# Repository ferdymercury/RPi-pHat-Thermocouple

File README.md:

# Raspberry Pi Thermocouple pHat for genmon

## Thanks!

First and foremost, this project is a derivation of the fine work done by
[Mike Lawrence](https://github.com/mikelawrence) with his
[RPi-pHat-Thermocouple](https://github.com/mikelawrence/RPi-pHat-Thermocouple)
project.  His implementation has a different use-case, and I adapted his
great design for my own purposes.

The major changes from his design to this one are:

* Change the form-factor from a Raspberry-Pi Zero sized board to a "full size"
  version intended for a Raspberry Pi 2 or Raspberry 3.
* Add an isolated RS-232 to TTL interface.
* Drop the on-board regulator to 5V, and associated bridge rectifier and "ideal
  diode".
* Drop the SPI EEPROM for automated "Hat" configuration.
* Drop the alarm buzzer.
* Add screw terminal connections for power, thermocouple, off-board 1-wire bus
  peripherals and RS-232 connections.
* Add pin headers for driving LED annunciators.
* Add pin headers (with configurable pull-ups) for end-user supplied I2C
  peripherals.
* Add a fuse to protect connections to off-board peripherals.

**IMPORTANT**

Please note that all of the work described here is on the `genmon` branch 
of the git repository.  Make sure that you `git checkout genmon` if you
clone the repository to get this modified version.

I'd like to extend my thanks to [Mike](https://github.com/mikelawrence) for
sharing his work with the community under an [MIT license](LICENSE).  This
derivitive project is likewise available under the same license.  

# What it is

This is a Raspberry Pi PCB that supports:

* Three MAX31850 1-Wire Thermocouple Converters for remote temperature sensing
* DS18S20 1-Wire Thermometer for local Hat temperature
* Electrically isolated RS-232 interface to the Raspberry Pi's serial port UART.

The goal of this board is to piggyback on a Raspberry Pi running the
[genmon](https://github.com/jgyates/genmon) package.  That software expects to
communicate with the 9600 bps RS-232 serial MODBUS connection on a Generac
generator controller.

Additionally, there are 3 type K thermocouple interfaces which can be used to
monitor critical temperatures in the generator, such as the oil cooler
temperature, exhaust air temperature, body temperatore of the generator, etc.

# Why it is

I have a 22kW generator manufactured by Generac, propane fueled.  The addition
of the wonderful [genmon](https://github.com/jgyates/genmon) has really added
significant value, and allowed me to integrate the generator with my [Home
Assistant](https://home-assistant.io) home automation platform.

On one occasion, I was experiencing an extended power outage, and of course, the
generator automatically started and switch the home loads to it.  About 6 hours
into this power outage, I was wondering how it was working.  The
[genmon](https://github.com/jgyates/genmon) software provides a bunch of data on
the current operation, indicating no alarms or faults.  However, after an
extended run time, I was wondering if the generator was overheating or otherwise
being stressed?

Measuring some of the relevant components had to be done with, *e.g.,*
thermocouples since the usual Dallas Semiconductor/Maxim 1-wire bus temperature
sensors wouldn't work in a high temperature environment. It was at that time
that I stumbled upon Mike Lawarence's work and decided to adapt it.

The first thing that caused me to want to layout a new board was that my use
case was different.  I had no need for a buzzer since my Raspberry Pi was buried
inside the generator enclosure and wouldn't ever be heard.  Further, I *really*
wanted to have screw terminals for the thermocouple wires since the metal alloys
used in the thermocouple wires don't take solder easily.  Due to the vibration
inherit to the environment, I wanted to have a really robust mechanical solution
for those connections.

Finally, The Raspberry Pi running [genmon](https://github.com/jgyates/genmon)
requires a conneciton to the RS-232 signals on the generator controller's MODBUS
interface.  At present, I was using an external TTL/RS-232 level convertor for
this purpose.  However in connecting this up, I create a ground loop -- there's
a ground path from the generator controller through the RS-232 level converter,
though the Raspberry Pi, through the 12V to 5V USB power support, to the
negative battery terminal, and finally through the cable from the battery to the
generator starter and control electronics.  I shudder to think how this all
behaves when the starter kicks in during a generator start-up sequence.

So this led to an isolated RS-232 to TTL level converter.  There is a separate
power support for this part of the circuit, intended to be supplied by power
available on the generator controller's MODBUS accessory connector.  There is an
high-speed isolation device (apparently transformer coupled?) rated at
approximately 20MBit/s, substantially higher bandwidth than most common
optoisolators.  This isolation device has separate power/ground connections for
each side, and in excess of 1kV of isolation.

# Status

A schematic for this circuit is available in [PDF format](RPi-pHat-Thermocouple.pdf)
so you don't need to use KiCAD to casually examine what's going on.

## Genmon variation

* Rev 3.1 of the PCB fixes pin assignment problems on the Maxim MAX3221
  RS-232/TTL level converter device.
  * You can order parts from Mouser using this [shared
    BOM](https://www.mouser.com/ProjectManager/ProjectDetail.aspx?AccessID=b36514df12)
    link. 
* Rev 3.0 PCB was the first version of the whole redesign, manufactured by
  JCLPCB.

Please note that all of the work described here is on the `genmon` branch 
of the git repository.  Make sure that you `git checkout genmon` if you
clone the repository to get this modified version.

## Original version
Older versions described below are Mike Lawrence's original design in the smaller Raspberry Pi Zero sized
form factor.

* Rev 2.0 PCB has been ordered from OSH Park and has been fully tested.
  * Removed one of the four MAX31850K's.
  * Increased thermocouple input filtering buy adding ferrite beads and a larger capacitor.
  * Added more filtering to thermocouple side of MAX31850K's.
  * Added DC Power connector and switching power supply that powers both the Raspberry Pi and the Hat.
  * The noisy reading the MAX31850K's occasionaly get are reduced in this version but not gone.
  * You can order parts from Mouser using this [shared BOM](https://www.mouser.com/ProjectManager/ProjectDetail.aspx?AccessID=bd69c35967).
  * You can order the PCB from OSH Park using this [link](https://oshpark.com/shared_projects/meYar6Ji).
* Rev 1.2 PCB has been ordered from OSH Park and tested.
  * Discovered the MAX31850K's get a noisy reading about 0.1% of the time. This noise is typically within 5 C but sometimes is greater than 30 C. Adding capacitors did little to help the Rev 1.1 design so most of the 3.3V power was switched to a 3.3V LDO regulator in an attempt to reduce the noise on the 3.3V power seen by the MAX31850K's.
  * You can order parts from Mouser using this [shared BOM](http://www.mouser.com/ProjectManager/ProjectDetail.aspx?AccessID=7612d46eeb).
  * You can order the PCB from OSH Park using this [link](https://oshpark.com/shared_projects/S5a4ZDvw).
* Rev 1.1 PCB was never built.
  * Added a pulldown on the alert signal to prevent the Alert buzzer from sounding on power on.
  * Added an on board DS18S20.
* Rev 1.0 PCB has been ordered from OSH Park and tested.
  * Discovered the linux kernel doesn't seem to support MAX31850K devices without a DS18S20 present. The kernel detects the MAX31850K devices but does not create a w1_slave file to read the temperature. This is most likely a bug in the Linux W1 driver.

# Kicad Notes

* This PCB design uses some libraries available here [Mike's KiCad Libraries](https://github.com/mikelawrence/KiCad-Libraries).
* This PCB was designed with [KiCad 5.1.5](http://kicad.org).
* The MAX31850K parts have an exposed pad on the bottom which requires either a
  reflow oven or hot air to solder properly.  Be careful to not apply too much
  solder paste to this pad.

# Design

## Input Power

This board has screw terminals to which you can connect a **regulated 5VDC**
power supply.  This is is connected **directlly** to the +5V power pins on the
Raspberry Pi GPIO connector.

**You should _never_ connect 5V DC power to the screw terminals if the Raspberry
Pi is being powered via it's USB connector!**

If the Raspberry Pi is powered in the usual way via its micro USB connector,
then the Raspberry Pi will supply power to this PCB and power the components on
the board.  Alternatively, if it is more convienient to provide regulated +5V DC
power from another source, then the screw terminals are available for that
purpose.

The components on the board draw well under 100mA of power at 5V, so there ought
to be no concern when powering from the Raspberry Pi that the PCB is plugged
into.

## Isolated RS-232 interface

Separately, there is a 4 pin screw terminal connection for RS-232 transmit and
receive as well as generator controller ground and generator controller 5VDC.
The ground and power on this 4 position screw terminal is isolated and distinct
from the Raspberry Pi power and the rest of the PCB.  You should not tie the
ground on the RS-232 screw termainal block to any other ground connection on the
genmon PCB.

## MAX31850K Thermocouple-to-Digital Converter

Although the MAX38150K datasheet typical application circuit doesn't show the
use of ferrite beads many designs seems to include them. That in combination
with the larger than normal capacitor across the input will hopefully improve
sampling errors even further.

# Raspberry Pi Setup

This setup makes several assumptions. First you are using Raspbian Buster. This
software and instructions most likely work on other versions of Raspbian but
they have not been tested. Second Python3 is the target programming environment.
It is also assumed that you are using the standard `pi` user. Otherwise you will
have to edit the commands by replacing `/home/pi` with your user's home
directory. Install everything needed by executing the following commands.

```text
sudo apt update
sudo apt -y install git python3-rpi.gpio python3-w1thermsensor python3-paho-mqtt
```

## Get the repository from Github

Clone this repository from Github with the following commands.

```text
cd /home/pi
git clone https://github.com/lmamakos/RPi-pHat-Thermocouple
git checkout genmon
```

## Setup Interfaces

For this Hat you will need to enable the 1-Wire interface. From the command line type
`sudo raspi-config` and follow the prompts to install  support in the kernel.

It's time to reboot your Raspberry Pi with `sudo reboot`.

## Test the 1-Wire Temperature Sensors

[Python3-w1thermsensor](https://github.com/timofurrer/w1thermsensor) is a nice 1-Wire python library that also supports command line reading of temperatures from 1-Wire devices. You should have already installed this package in the [Raspberry Pi Setup](#Raspberry-Pi-Setup) section.

Test the single on-board DS18B20 temperature sensor using `w1thermsensor all --type DS18S20`.

```text
pi@studio-fridge:~ $ w1thermsensor all --type DS18S20
Got temperatures of 1 sensors:
  Sensor 1 (00080372f2c4) measured temperature: 28.06 celsius
```

Now test the three MAX38150Ks temperature sensor by using `w1thermsensor all --type MAX31850K`.

```text
pi@studio-fridge:~ $ w1thermsensor all --type MAX31850K
Got temperatures of 3 sensors:
  Sensor 1 (000000181928) measured temperature: 23.75 celsius
  Sensor 2 (00000018192b) measured temperature: 24.0 celsius
  Sensor 3 (000000181d59) measured temperature: 2047.81 celsius
```

The 2047.81 celsius reading is what you get when there is no thermocouple connected to the MAX31850K.

# Integration with other software packages and systems

## Integration with [genmon](https://github.com/jgyates/genmon)

The primary motivation for this board's design is to support the use of
[genmon](https://github.com/jgyates/genmon) running on a Raspberry Pi 2 Model B,
Raspberry Pi 3 Model B, or a Raspberry Pi Zero.  It includes two major
functional elements:

1. Three (3) connections for Type-K thermocouples, using a Maxim 1-wire bus
   attached controller.
2. A TTL to RS-232 level converted to connect the Raspberry Pi serial port to
   the MODBUS connection on the generator controller.

### Thermocouples

These are intended to enable monitoring of high-temperature points within the
Generac generator, such as the temperature of the engine oil cooler, engine
block, generator temperature or perhaps exhaust temperature.

The use of Type-K thermocouples permits the measurement of very high
temperatures, as high as 700 °C.  As a practical matter, the maximum temperature
is limited by the insulation and jacket on the cabling connecting to the
thermocouple junction.  Typically, thermocouple products with cables rated to
400 °C are easily available and inexpensive.

**VERY IMPORTANT** - the MAX 31855K thermocouple interface devices does not
support *grounded thermocouples* - where the junction of the thermocouple is
electrically connected to the power supply ground.  In particular, the sensor
device does a diagnostic test checking for an "open" connection at the
thermocouple terminals, as well as a short to ground or the *V<sub>dd</sub>*
power supply on the board.

It's common to see either exposed junction thermocouples, or where the actual
thermocouple junction is within a metal tube or other mechanical arrangement.
The junction is deliberately tied to the case (which presumably is in contact
with the thing you're trying to measure) for better thermoconducivity, making it
more responsive to temperature changes.  Additionally some thermocouple probe
arrangements have a woven metalic armor shield on the cable, which is also
electrically tied to the thermocouple junction. If these armored cables come in
contact with each other, this will also cause a fault.

It is recommended that you choose a Type-K thermocouple with a high (enough)
temperature rated cable, and either have the thermocouple junction be in free
space, or insulated from the chassis of the generator.

One possibility if you use the inexpensive generic thermocouple probes is to
form a small bead of high temperature expoxy around the junction, or affix the
the junction with non-conductive expoxy to the surface you're trying to perform
temperature measurements on.

### DS18B20 or DS18S20 1-wire bus sensors

Why not the usual Maxim DS18B20 one-wire bus temperature sensors?  These
semiconductor devices are packaged in plastic material for their packages, and
not rated for these high temperatures present in some parts of the generator.
However, there are other temperatures that might usefully be monitored, such as
the outside air temperature and these DS18B20 devices are entirely suitable for
that purpose.  One of these devices is present on the printed circuit board to
monitor the temperature nearby the Raspberry Pi.

### Isolated RS-232C to TTL serial converter

This board features a level converter to connect the RS-232C serial signals on
the generator's MODBUS accessory connector to the 3.3V TTL signal levels needed
by the Raspberry Pi's serial interfaces.

Most significantly, this serial interface is electrically isolated from the
Raspberry Pi and its power supply.  The RS-232 "side" is powered by the +5V /
Ground connections avialable on the MODBUS connector.  This power supply is used
to run the RS-232 level converter, and half of an isolation device which couples
the transmit and receive signals to the "other" side of the board which shares a
power supply (and ground) with the Raspberry Pi.  This isolation means that you
no longer need to worry about ground loops or powering the Raspberry Pi from
some other power source not electrically tied to the generator's power supply
and ground.

## Integration with [Home Assistant](https://home-assistant.io)

(Future) software will sample the thermocouples and 1-wire temperature sensors
and publish the values to MQTT for Home Assistant or other applications to
access.

A deliberate choice is that there is no in-built policy for over-temperature or
under-temperature warnings or actions.  The goal is to  publish these values to
be acted upon or displayed by other applications.

# Installation of the board

The board is intended to plug into the 40 pin GPIO connection available on all
the recent models of Raspberry Pi computers.   (The notable exception is the
original Raspberry Pi Model A which has a 26 pin GPIO connector.)  While it may
be possible to install a 26 pin connector on this board for that device, this
has not been tested.

Reference this rendering of the board:

### J2 - GPIO Connector

The connector mounted in this position plugs into the 40 pin GPIO expansion
connector on the Raspberry Pi.  When mounted correctly, this board sits directly
over the Raspberry Pi.

If you intend to build this board, remember that the GPIO connector is mounted
on the *back* of the board.  In fact, this is the _only_ component on the back
side of the board.

### J1 - Raspberry Pi Power

This connector supplies power to the Raspberry Pi via pins on the GPIO
connector. It should be used **only** if the Raspberry Pi doesn't have a power
supply connected to the Micro USB connector on the Raspberry Pi.  

If used, you must supply regulated +5V DC power to the connector.  Note ***there
is no reverse polarity protection*** for power fed on these screw terminals.

Power for the board can also be supplied via the Raspberry Pi's expansion connector
via the +5V DC signal on pin 2 when the Raspberry Pi is powered via it's Micro USB 
connector.

When the the PCB is powered, the green `PWR` LED D5 should be illuminated.  This
LED is conneted to the locally regulated 3.3V DC power supply for the devices on
the board (excluding the RS-232 interface; see below.)

### J3, J4, J5 - Thermocouple connections

These screw terminals are labeled **TC1**, **TC2** and **TC3**, and are
polarized.  The Type-K thermocouples connected to each of these terminals are
polarized and the positive and negative signals are labeled on the board.

The wires on the thermocouple care are usually marked or color-coded to indicate
the positive and negative termainals.  Connecting the thermocouple with reverse
polarity will not damage the board or thermocouple, but will yield incorrect
measurements.

### J7 - Generator Controller Serial Connection

Signals from the Generac generator's controller are connected to J7.  This includes the RS-232 data connections and power-supply for the isolated RS-232 interface.

An important aspect of this port, and this part of the circuit, is the electrial
isolation of the generator connection from the Raspberry Pi and the rest of the
circuit.  This interface consists of a RS-232 level converter (+/- 5V) to TTL (0
to 3.3 volts), and an isolation device that literally bridges a gap on the PCB.
The power and ground connections of this serial interface are isolated from the
power and ground connections of the Raspberry Pi and rest of the circuit.

* **RX in** this terminal is for receiving the data transmitted *from* the generator
*to* genmon.   This should be connected to pin 8 of the controller's molex connector.
* **RX out** this terminal is the *output* data transmitted *to* the generator from genmon.  This should be connected to pin 7 of the controller's molex connector.

* The **Ground** terminal should be connected to pin 2 of the controller's molex connector.
* The **5V** terminal should be connected to pin 1 of the controller's molex
  connector, which is a power source intended to power accessories.  This
  circuit requires approximately 50mA (or less) from the power input.  While a
  nominal +5V DC source is expected, there is an internal low-dropout (LDO)
  regulator on the board that should function with a 4V - 16V DC power input.
  Do not exceed 16VDC input.  This power supply connection includes a
  reverse-polarity protection diode.

When power is correctly connected, a green LED `Gen PWR` D20 should illuminate.

### J6 - External 1-wire bus connector

External 1-wire bus temperature sensors can be connected to J6.  There is
regulated +3.3V power on this connector, supplied through a 100mA resettable
thermal fuse.  This power source is intended to supply only low-power sensor
devices.

Note that the usual Maxim DS18B20 sensors are measuring temperatures between
-55C to +125C.

### J8 - LED connector

This connector is intended to drive up to 6 LEDs to be used to indicate generator status.  A selection of the Raspberry Pi CPU's GPIO signals are present: 23, 24,25, 8, 9, 7 as marked on the PCB above the connector location.  The corresponding pins below are all connected to ground.

Each active (non-ground) pin on the connector is driven through a 330 ohm current limiting resistor.  This is to try to avoid over-current situations which could damage the drivers on the CPU chip.

A 1.8V voltage drop LED should be suitable for use (which may exclude any blue
LEDs).  Typical current through the LED will be 4.5mA; while not terribly bright, this may be useful as a local status indication.

Of course, these signals could also be used to drive, e.g., a MOSFET device, to drive a higher-current load.

One possibility for using this connector to drive one or more LEDs is the
gengpio.py program, suitably configured.  
(See https://github.com/jgyates/genmon/wiki/1----Software-Overview#gengpiopy-optional )

Note that when using these signals, they can be identified by either the GPIO signal number or the pin number on the Raspberry Pi's expansion connector.  This document
only references the CPU GPIO number.

### J9 I2C expansion connector

This connector exposes an I2C interface on the Raspberry Pi's CPU for some 
future unspecified use.  By default, there are pull-up resistors on the **SDA** and 
**SCL** signals on the connector, as well as (fused) +3.3V DC and Ground.

* SDA signal is connected directly to GPIO2 (pin 3 on the Raspberry Pi connector)
* SCL signal is connected directly to GPIO3 (pin 5 on the Raspberry Pi connector)

If pull-ups on the SCL and SDA signals are not desired, then jumper traces s on
*the back* of the PCB can be cut to disconnect the pull-up resistors.

# NO WARRANTY

This project was created for my personal use, but it is available under a
permissive [license](LICENSE) to anyone interested.

This software, hardware designs and other information are provided for
educational and informational purposes only. Connecting any device to a Raspberry
Pi or generator carryies risk, and you should understand those risks before
undertaking that action.  Interconnection of this design to any other devices
provided by any manufacturer may void any warrantee offered by a manufacturer,
or cause damage if performed.  You are solely responsible for exercising due
care and caution when choosing to use these designs and other information
provided here.

**THIS HARDWARE DESIGN, SOFTWARE AND OTHER MATERIAL IS PROVIDED BY THE COPYRIGHT
HOLDERS AND CONTRIBUTORS “AS IS” AND ANY EXPRESS OR IMPLIED WARRANTIES,
INCLUDING, BUT NOT LIMITED TO, THE IMPLIED WARRANTIES OF MERCHANTABILITY AND
FITNESS FOR A PARTICULAR PURPOSE AND NONINFRINGEMENT ARE DISCLAIMED. IN NO EVENT
SHALL THE COPYRIGHT OWNER OR CONTRIBUTORS BE LIABLE FOR ANY DIRECT, INDIRECT,
INCIDENTAL, SPECIAL, EXEMPLARY, OR CONSEQUENTIAL DAMAGES (INCLUDING, BUT NOT
LIMITED TO, PROCUREMENT OF SUBSTITUTE GOODS OR SERVICES; LOSS OF USE, DATA, OR
PROFITS; OR BUSINESS INTERRUPTION) HOWEVER CAUSED AND ON ANY THEORY OF
LIABILITY, WHETHER IN CONTRACT, STRICT LIABILITY, OR TORT (INCLUDING NEGLIGENCE
OR OTHERWISE) ARISING IN ANY WAY OUT OF THE USE OF THIS SOFTWARE OR HARDWARE
DESIGNS OR OTHER MATERIALS, EVEN IF ADVISED OF THE POSSIBILITY OF SUCH DAMAGE.**

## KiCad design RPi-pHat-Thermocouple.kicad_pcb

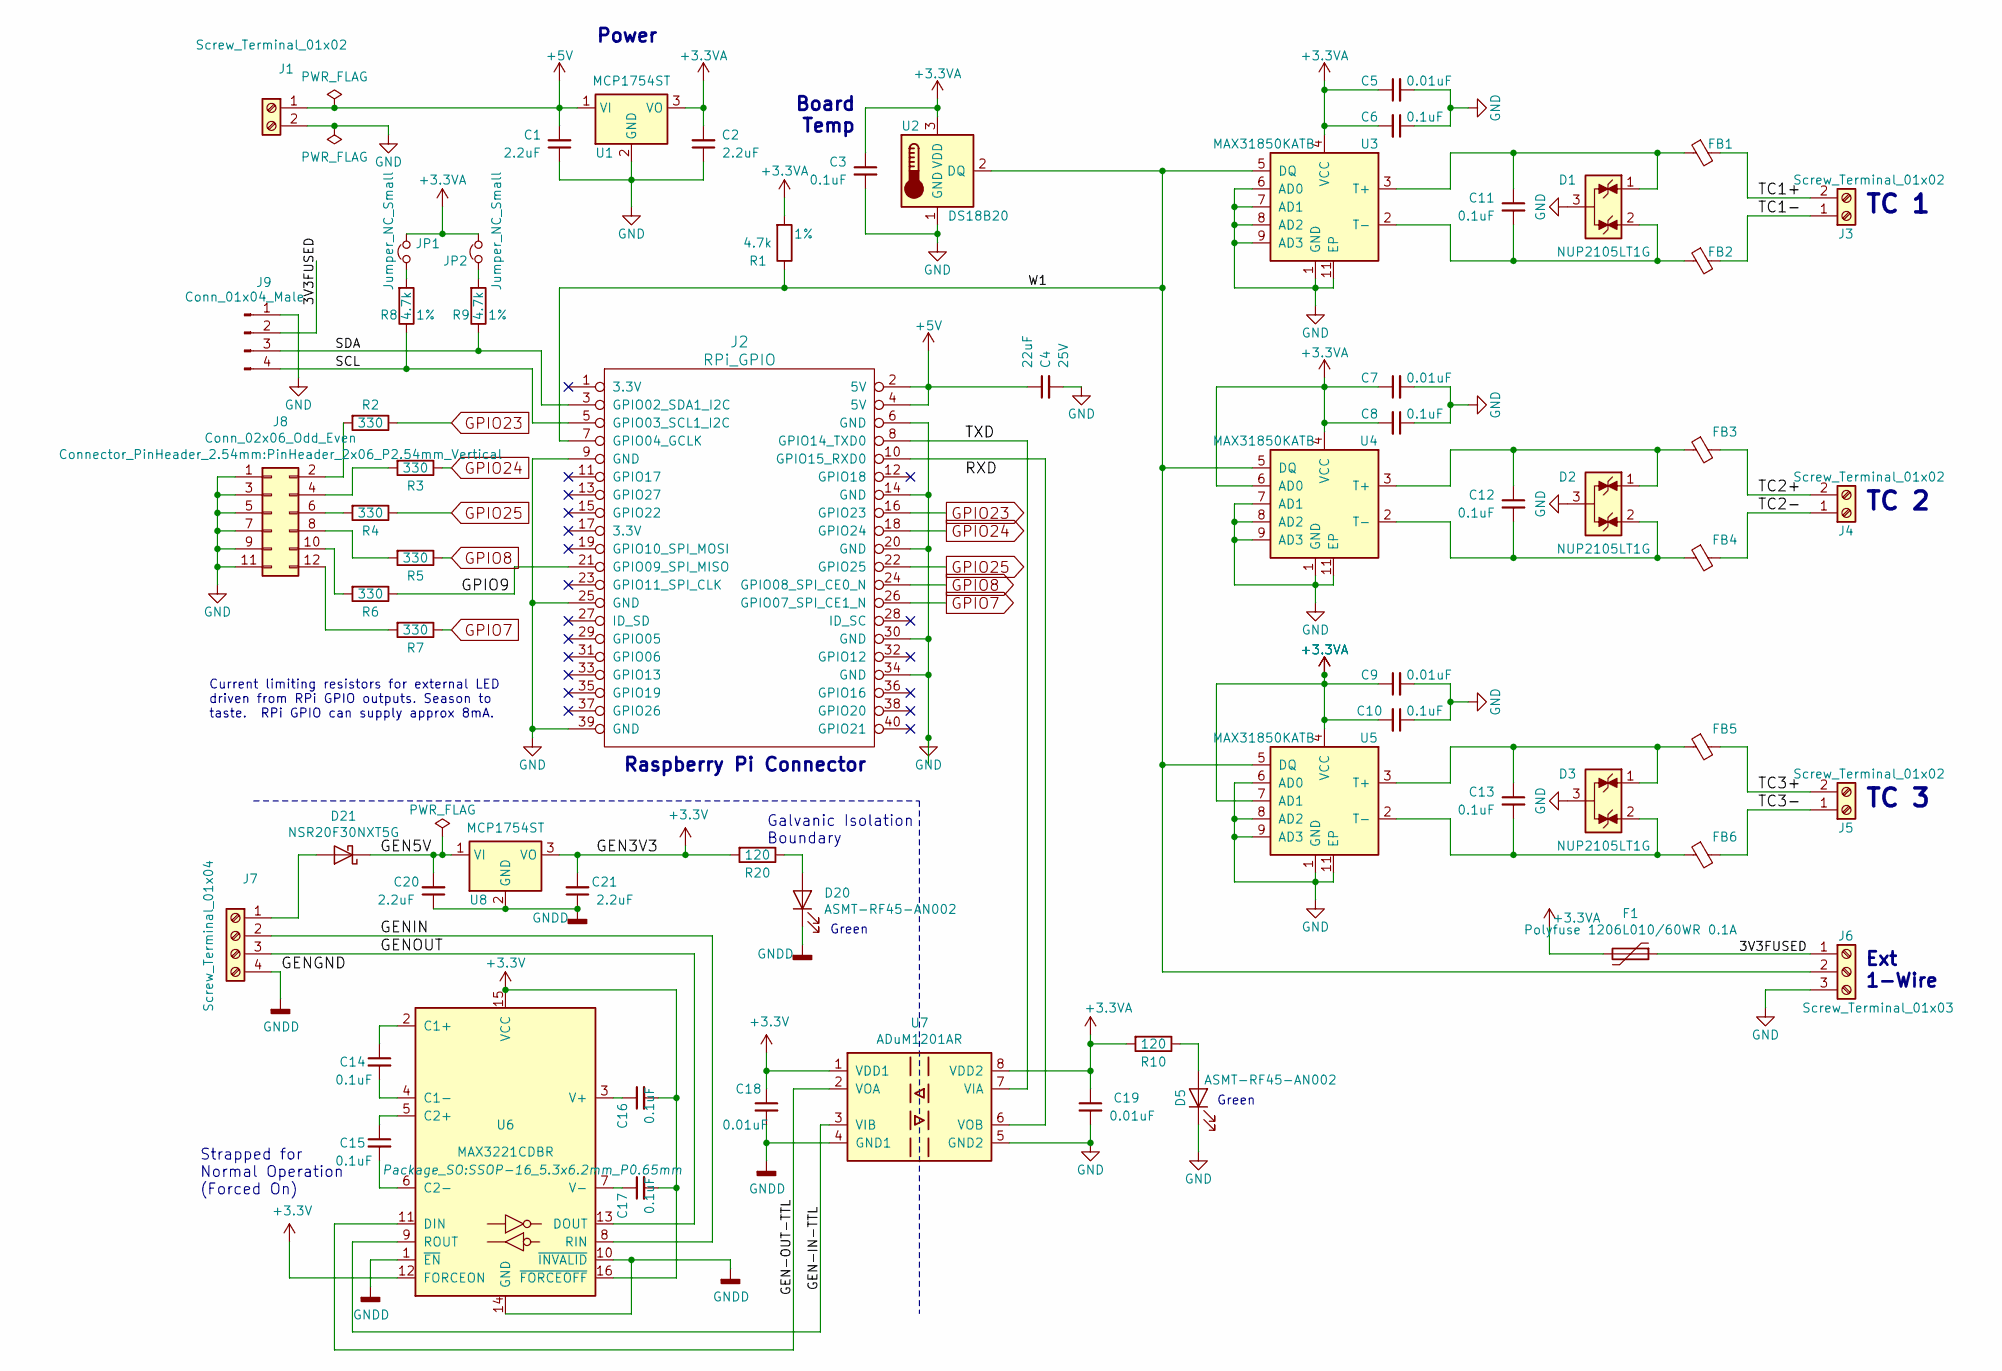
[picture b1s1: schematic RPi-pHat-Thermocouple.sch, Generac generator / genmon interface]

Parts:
C1, C2, C20, C21: 2.2uF; C_0805_2012Metric; Part Number CC0805KKX7R7BB225
C3, C6, C8, C10, C11, C12, C13, C14, C15, C16, C17: 0.1uF; C_0603_1608Metric; Part Number CC0603KRX7R9BB104
C4: 22uF; C_0805_2012Metric; Voltage 25V; Tolerance 20%; Part Number TMK212BBJ226MG-TT
C5, C7, C9, C18, C19: 0.01uF; C_0603_1608Metric; Part Number CC0603KRX7R9BB103
D1, D2, D3: NUP2105LT1G; SOT-23; Part Number NUP2105LT1G
D5, D20: ASMT-RF45-AN002; LED_0603_1608Metric; Part Number ASMT-RF45-AN002
D21: NSR20F30NXT5G; D_0603_1608Metric; Part Number NSR20F30NXT5G
F1: Polyfuse 1206L010/60WR 0.1A; Fuse_1206_3216Metric_Pad1.42x1.75mm_HandSolder; Part Number 1206L010/60WR; Mouser 576-1206L010/60WR
FB1, FB2, FB3, FB4, FB5, FB6: 1k; L_0603_1608Metric; Part Number MMZ1608B102CTD25
J1, J3, J4, J5: Screw_Terminal_01x02; TerminalBlock_Phoenix_PT-1,5-2-3.5-H_1x02_P3.50mm_Horizontal; Part Number 1984617
J2: RPi_GPIO; PinSocket_2x20_P2.54mm_Vertical; Part Number 2222
J6: Screw_Terminal_01x03; TerminalBlock_Phoenix_PT-1,5-3-3.5-H_1x03_P3.50mm_Horizontal; Part Number 1984620
J7: Screw_Terminal_01x04; TerminalBlock_Phoenix_PT-1,5-4-3.5-H_1x04_P3.50mm_Horizontal; Part Number 1984633
J8: Conn_02x06_Odd_Even; PinHeader_2x06_P2.54mm_Vertical; Part Number M20-9760642
J9: Conn_01x04_Male; PinHeader_1x04_P2.54mm_Vertical; Part Number M20-9990445
JP1, JP2: Jumper_NC_Small; SolderJumper-2_P1.3mm_Bridged_RoundedPad1.0x1.5mm
R1, R8, R9: 4.7k; R_0603_1608Metric; Tolerance 1%; Part Number AC0603FR-074K7L
R2, R3, R4, R5, R6, R7: 330; R_0603_1608Metric; Tolerance 1%; Part Number RC0603FR-07330RL
R10, R20: 120; R_0603_1608Metric; Tolerance 1%; Part Number RC0603FR-07120RL
U1, U8: MCP1754ST; SOT-89-3; Part Number MCP1754ST-3302E/MB
U2: DS18B20; TO-92; Part Number DS18B20+
U3, U4, U5: MAX31850KATB; TDFN-10-1EP_3x4mm_Pitch0.5mm; Part Number MAX31850KATB+
U6: MAX3221CDBR; SSOP-16_5.3x6.2mm_P0.65mm; Part Number MAX3221CDBR
U7: ADuM1201AR; SOIC-8_3.9x4.9mm_P1.27mm; Part Number ADUM1201AR

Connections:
+3.3VA: C2.2, C3.1, C5.1, C6.2, C7.1, C8.2, C9.1, C10.2, C19.1, F1.2, JP1.2, JP2.2, R1.2, R10.2, U1.3 (VO), U2.3 (VDD), U3.4 (VCC), U4.4 (VCC), U4.6 (AD0), U5.4 (VCC), U5.7 (AD1), U7.8 (VDD2)
+3V3: C16.2, C17.2, C18.1, C21.2, R20.2, U6.12 (FORCEON), U6.15 (VCC), U6.16 (~FORCEOFF), U7.1 (VDD1), U8.3 (VO)
+5V: C1.2, C4.1, J1.1, J2.2 (5V), J2.4 (5V), U1.1 (VI)
/3V3FUSED: F1.1, J6.1, J9.2
/GEN5V: C20.2, D21.1 (K), U8.1 (VI)
/GEN-IN-TTL: U6.9 (ROUT), U7.3 (VIB)
/GEN-OUT-TTL: U6.11 (DIN), U7.2 (VOA)
/GENIN: J7.2, U6.8 (RIN)
/GENOUT: J7.3, U6.13 (DOUT)
/GPIO9: J2.21 (GPIO09_SPI_MISO), R6.1
/SCL: J2.5 (GPIO03_SCL1_I2C), J9.4, R8.1
/SDA: J2.3 (GPIO02_SDA1_I2C), J9.3, R9.1
/TC1+: FB1.2, J3.2
/TC1-: FB2.2, J3.1
/TC2+: FB3.2, J4.2
/TC2-: FB4.2, J4.1
/TC3+: FB5.2, J5.2
/TC3-: FB6.2, J5.1
/TXD: J2.8 (GPIO14_TXD0), U7.7 (VIA)
/W1: J2.7 (GPIO04_GCLK), J6.2, R1.1, U2.2 (DQ), U3.5 (DQ), U4.5 (DQ), U5.5 (DQ)
GND: C1.1, C2.1, C3.2, C4.2, C5.2, C6.1, C7.2, C8.1, C9.2, C10.1, C19.2, D1.3 (A), D2.3 (A), D3.3 (A), D5.1 (K), J1.2, J2.6 (GND), J2.9 (GND), J2.14 (GND), J2.20 (GND), J2.25 (GND), J2.30 (GND), J2.34 (GND), J2.39 (GND), J6.3, J8.1, J8.3, J8.5, J8.7, J8.9, J8.11, J9.1, U1.2 (GND), U2.1 (GND), U3.1 (GND), U3.6 (AD0), U3.7 (AD1), U3.8 (AD2), U3.9 (AD3), U3.11 (EP), U4.1 (GND), U4.7 (AD1), U4.8 (AD2), U4.9 (AD3), U4.11 (EP), U5.1 (GND), U5.6 (AD0), U5.8 (AD2), U5.9 (AD3), U5.11 (EP), U7.5 (GND2)
GNDD: C18.2, C20.1, C21.1, D20.1 (K), J7.4, U6.1 (~EN), U6.10 (~INVALID), U6.14 (GND), U7.4 (GND1), U8.2 (GND)
GPIO7: J2.26 (GPIO07_SPI_CE1_N), R7.1
GPIO8: J2.24 (GPIO08_SPI_CE0_N), R5.1
GPIO23: J2.16 (GPIO23), R2.1
GPIO24: J2.18 (GPIO24), R3.1
GPIO25: J2.22 (GPIO25), R4.1
unnamed: C11.1, D1.1 (K), FB1.1, U3.3 (T+)
unnamed: C11.2, D1.2 (K), FB2.1, U3.2 (T-)
unnamed: C12.1, D2.1 (K), FB3.1, U4.3 (T+)
unnamed: C12.2, D2.2 (K), FB4.1, U4.2 (T-)
unnamed: C13.1, D3.1 (K), FB5.1, U5.3 (T+)
unnamed: C13.2, D3.2 (K), FB6.1, U5.2 (T-)
unnamed: C14.1, U6.2 (C1+)
unnamed: C14.2, U6.4 (C1-)
unnamed: C15.1, U6.5 (C2+)
unnamed: C15.2, U6.6 (C2-)
unnamed: C16.1, U6.3 (V+)
unnamed: C17.1, U6.7 (V-)
unnamed: D5.2 (A), R10.1
unnamed: D20.2 (A), R20.1
unnamed: D21.2 (A), J7.1
unnamed: J2.10 (GPIO15_RXD0), U7.6 (VOB)
unnamed: J8.2, R2.2
unnamed: J8.4, R3.2
unnamed: J8.6, R4.2
unnamed: J8.8, R5.2
unnamed: J8.10, R6.2
unnamed: J8.12, R7.2
unnamed: JP1.1, R8.2
unnamed: JP2.1, R9.2

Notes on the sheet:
TC 1
TC 2
TC 3
Power
Board Temp
Ext 1-Wire
Strapped for Normal Operation (Forced On)
Galvanic Isolation Boundary
Raspberry Pi Connector
Current limiting resistors for external LED driven from RPi GPIO outputs. Season to taste. RPi GPIO can supply approx 8mA.
Green

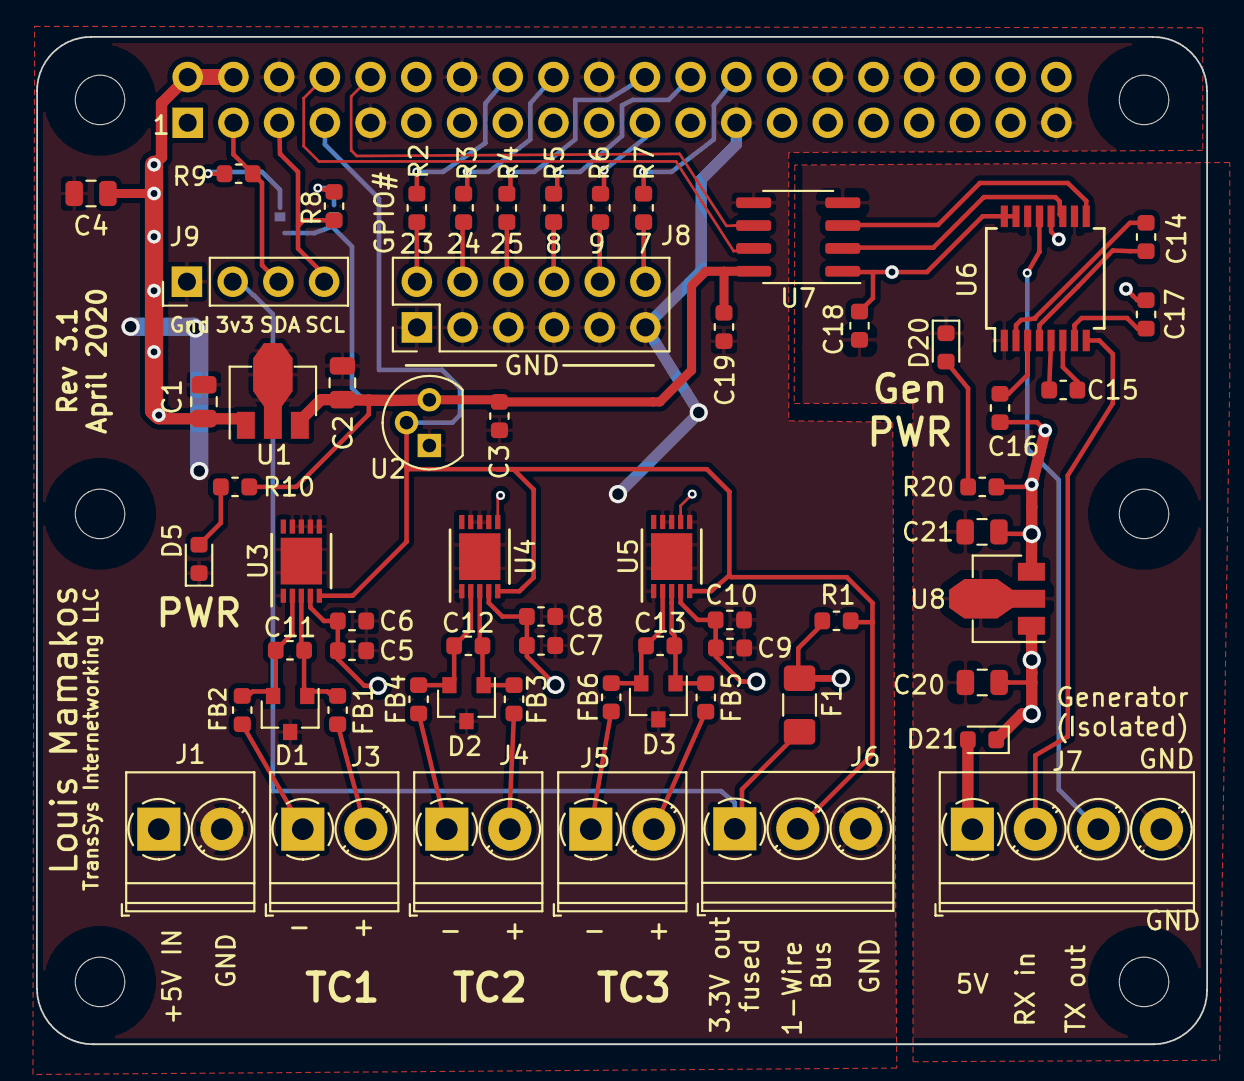
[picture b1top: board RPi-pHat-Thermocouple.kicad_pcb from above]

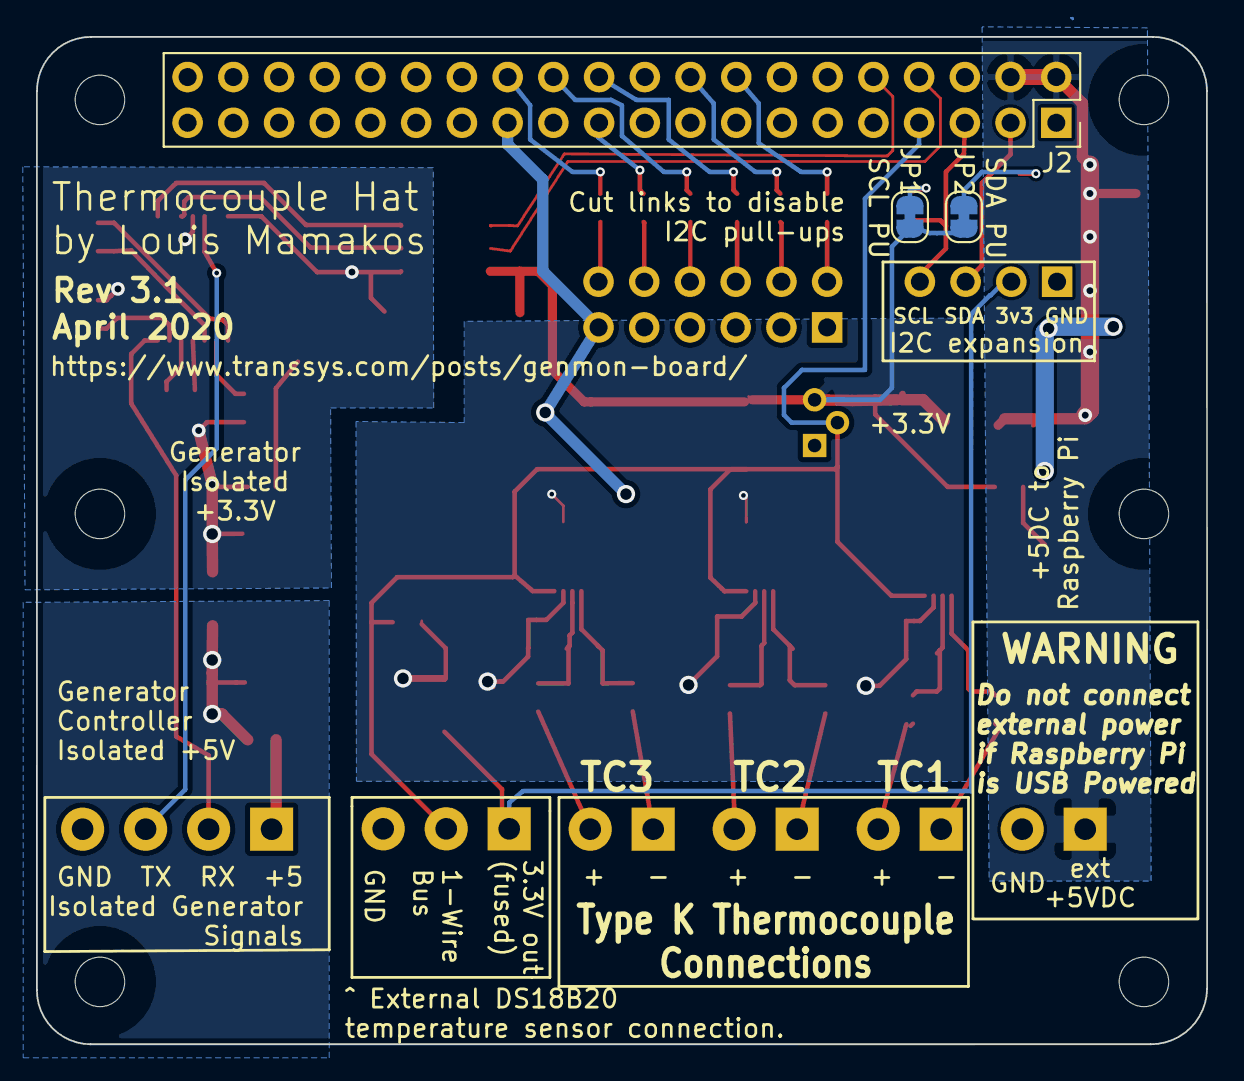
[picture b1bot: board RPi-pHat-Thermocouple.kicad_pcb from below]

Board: 2 copper layers, 65.0 x 56.0 mm, 70 parts (3 on the bottom side), 51 nets.

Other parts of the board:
h1, h2, h3, h4, h5, h6: RPi_Hat_Mounting_Hole

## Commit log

2019-10-04 Datasheets for new devices
2019-10-04 Variation for generator monitoring application.
    Remove buzzer and related; remove Pi Hat EEPROM.
    Since the form factor is going to expand a bit beyond the Pi-Hat
    specification to enable adding an isolated RS-232/TTL interface for
    the Raspberry Pi serial port, we'll remove the parts that are not needed
    for the generator-targeted application.
2019-10-04 ignore dsn and backup files
2020-04-06 PCB Version 3.0 files
2020-04-20 update datasheets for devices being used in design
2020-04-20 Deleted EEPROM from design, so no need for tools to program it
2020-04-20 Board image no longer representative since conversion to full-size Raspberry-Pi form factor
2020-04-20 Ignore some more files
2020-04-20 more unneeded files
2020-04-20 Candidate files for Version 3.1 of the PCB
2020-04-20 Documentation changes, first pass
2020-04-20 add/tweaked content in README.md doc. Still incomplete.
2020-04-21 minor edits to docs
2020-05-07 Update documentation
2020-05-07 add additional graphc
2020-05-07 update README documentation
2020-05-07 fix doc link
2020-05-07 fix link to genmon doc
2020-05-07 More doc updates
2020-05-07 clarify that all this is on the genmon branch of the repo
2020-05-19 data sheet updates
2020-05-19 update docs
2020-05-19 add some LCSC part numbers
2020-05-19 test program to drive LEDs on GPIO pins brought out to connector
2020-05-19 provide more info on detected faults; comment out unused code
2020-05-19 simple test program to read sensors and test library
2021-11-08 Update README.md
    https://forum.kicad.info/t/warning-avoid-all-links-to-kicad-pcb-org-use-kicad-org/31521
